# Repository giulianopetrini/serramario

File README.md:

# serramario
Programma per interfaccia gestione serra/orto

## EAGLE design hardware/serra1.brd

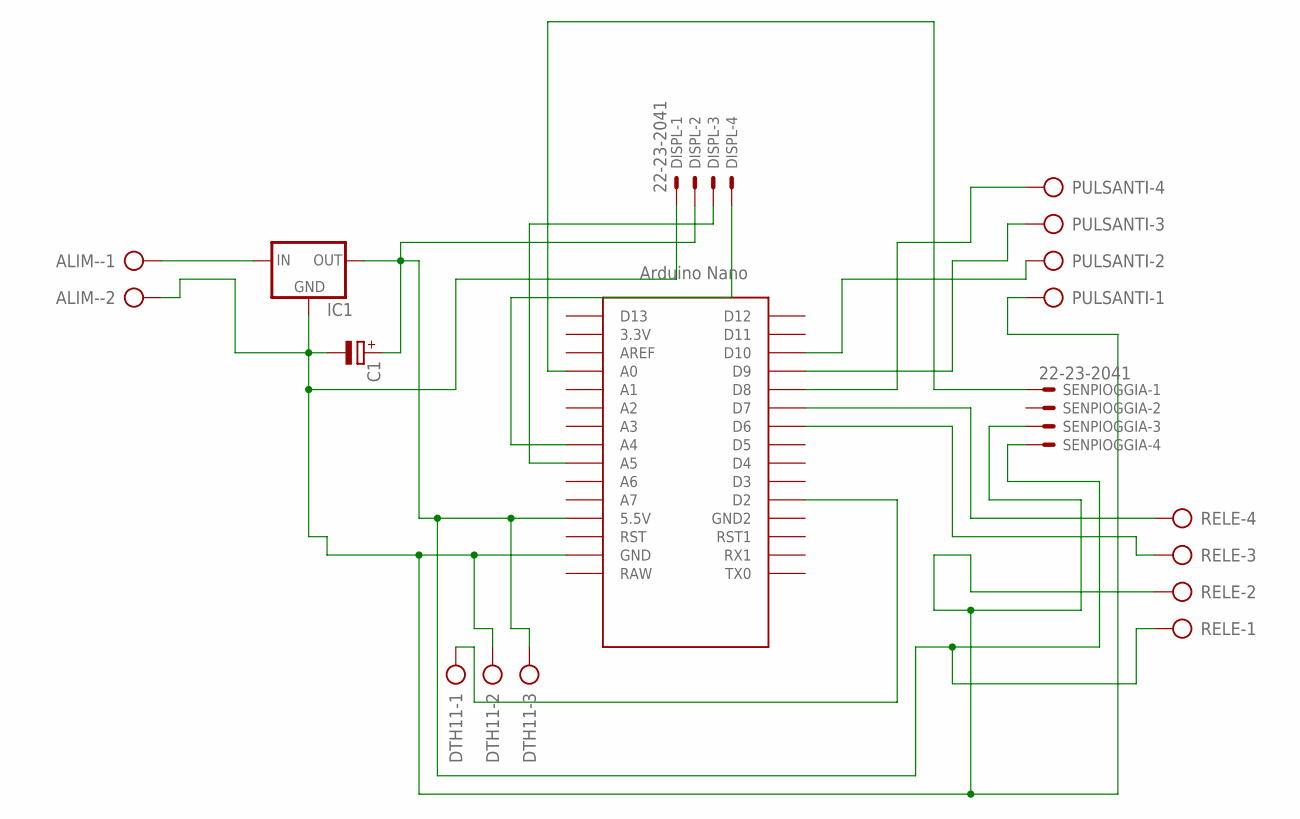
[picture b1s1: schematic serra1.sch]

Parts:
ALIM-: AK500/2
C1: CPOL-EUE5-13; E5-13
DISPL: 22-23-2041
DTH11: AK500/3
IC1: 78XXS
PULSANTI: AK500/4
RELE: AK500/4
SENPIOGGIA: 22-23-2041
U$1: NANO

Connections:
DTH11: C1.+, DISPL.2, DTH11.3, IC1.OUT, RELE.1, SENPIOGGIA.4, U$1.5V (5.5V)
unnamed: ALIM-.1, IC1.IN
unnamed: SENPIOGGIA.1, U$1.A0
unnamed: RELE.4, U$1.D7
unnamed: DISPL.3, U$1.A5
unnamed: PULSANTI.2, U$1.D10
unnamed: RELE.3, U$1.D6
unnamed: DISPL.4, U$1.A4
unnamed: DTH11.1, U$1.D2
unnamed: PULSANTI.4, U$1.D8
unnamed: PULSANTI.3, U$1.D9
unnamed: ALIM-.2, C1.-, DISPL.1, DTH11.2, IC1.GND, PULSANTI.1, RELE.2, SENPIOGGIA.3, U$1.GND

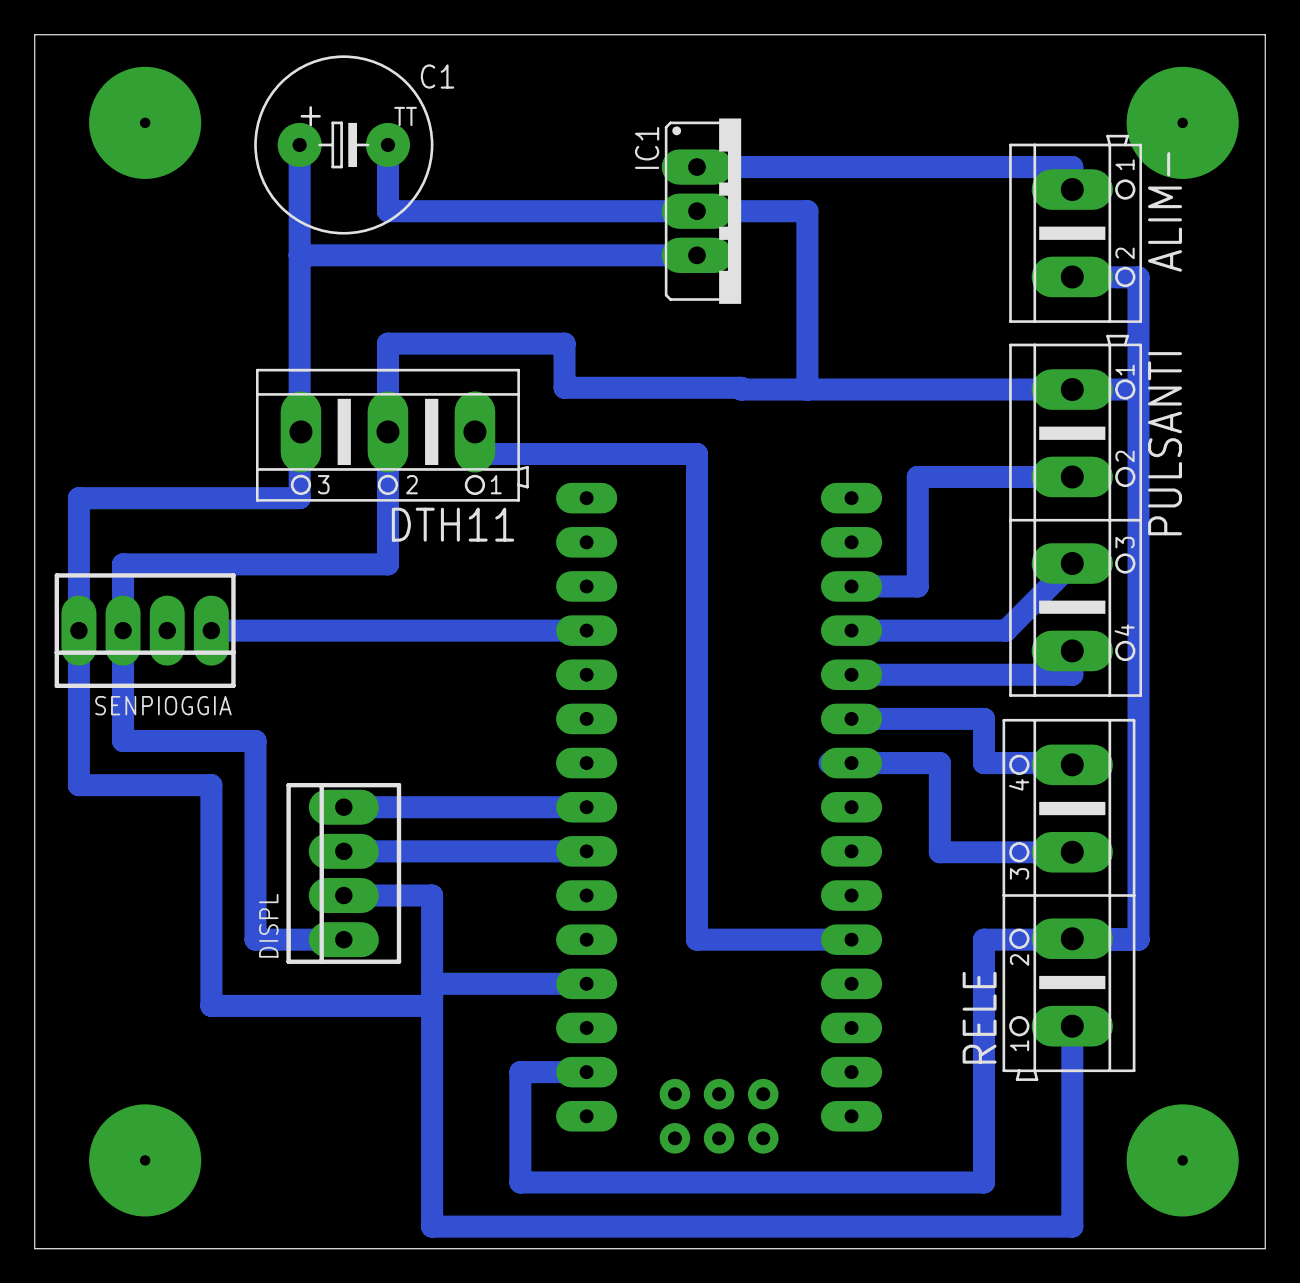
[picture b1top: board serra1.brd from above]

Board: 2 copper layers, 70.8 x 69.8 mm, 9 parts (0 on the bottom side), 12 nets.

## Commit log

2018-03-11 Primo Commit
    Inizio Programma
2018-03-11 Fix per antirimbalzo
    Fix funzione antirimbalzo per bottone aumenta e diminuisci temperatura
2018-03-11 Fix Messaggi Display
    Fix per messaggio di stato serra e ventilatore
2018-03-11 File Hardware
    Aggiunti file del prototipo hardware
